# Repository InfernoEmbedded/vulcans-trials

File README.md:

# 🔥 Vulcan's Trials (`vulcans-trials`)

**Vulkan GPU + Multithreaded CPU Auto-Placer & Auto-Router for KiCad**  
Published by **InfernoEmbedded** — Licensed under **GNU GPLv3 (`GPL-3.0-only`)**

---

<p align="center">
  
  <br>
  <em>▶️ <b>Watch Vulcan's Trials in Action:</b> Real-time 1080p Auto-Placement & Auto-Routing on the 4-layer P1P2ESP board (Click to play on YouTube)</em>
</p>

---

## Overview

**Vulcan's Trials** is a unified, hardware-accelerated PCB Auto-Placer and Auto-Router written in Rust for KiCad (`8.0` / `9.0` / `10.0`). It combines:

1. **Schematic-Aware Parallel Tempering Auto-Placer (`src/placer.rs`):**
   - Automatically parses sibling `.kicad_sch` files to extract functional circuit clusters (e.g., Buck Converter, Surge/ESD Front-End, Transceiver, MCU) and passive decoupling/bias affinities.
   - Enforces exact polygon courtyard clearances using Separating Axis Theorem (SAT) collision detection (`0` courtyard overlaps) while respecting locked components and off-board RF antenna overhang zones.
   - Minimizes ratsnest topological crossings and Euclidean Minimum Spanning Tree (MST) wirelength across all CPU cores using Parallel Tempering Simulated Annealing.

2. **Vulkan Compute + Negotiated-Congestion 3D Auto-Router (`src/vulkan.rs`, `src/router.rs`):**
   - Explicitly targets **Vulkan** (`wgpu::Backends::VULKAN`) with WGSL compute shaders (`DISTANCE_FIELD_WGSL`) to accelerate 2D obstacle Euclidean Distance Field transforms on the GPU.
   - Enforces bidirectional per-netclass clearance ($\max(\text{clearance}_A, \text{clearance}_B)$), project netclass track widths (Power, Differential Pairs, High-Speed Buses, Default), keepout zones, and fine-pitch SMD pad-to-via exclusions.
   - Generates deterministic staggered pin-escape stubs ($\Delta \ge 0.75\text{ mm}$) for fine-pitch QFN, BGA, and USB-C packages, plus automated ground-plane via stitching.
   - Supports dynamic component nudging (`NudgeEngine`) and multi-pass PathFinder negotiated-congestion rip-up and reroute.

3. **Real-Time Interactive GUI (`src/gui.rs`):**
   - Live 2D PCB viewport with pan/zoom, layer toggles (`F.Cu`, `B.Cu`, Courtyards, Ratsnest, Vias, Keepouts, Reference Designators), and live trial progress.
   - Real-time **CPU Load %** (`/proc/stat`) and **Vulkan GPU Load %** (`VulkanEngine` compute duty cycle + `nvidia-smi` / DRM sysfs) gauges and sparkline histories.

---

## Quick Start

### 1. Build Release Binary & Run Self-Test
```bash
git clone https://github.com/InfernoEmbedded/vulcans-trials.git
cd vulcans-trials
cargo build --release
./target/release/vulcans-trials --self-test
```

### 2. Launch the Interactive GUI
```bash
./target/release/vulcans-trials --input /path/to/board.kicad_pcb --output /path/to/board_routed.kicad_pcb
```

### 3. Run in Headless CLI Mode
```bash
# Auto-route only
./target/release/vulcans-trials --headless --mode route \
  --input /path/to/board.kicad_pcb \
  --output /path/to/board_routed.kicad_pcb

# Full Trial (Auto-Place + Auto-Route)
./target/release/vulcans-trials --headless --mode both --duration 30 \
  --input /path/to/board.kicad_pcb \
  --output /path/to/board_vulcan.kicad_pcb
```

### 4. KiCad Action Plugin Installation

#### Option A: KiCad Plugin and Content Manager (PCM)
In KiCad (8.0, 9.0, or 10.0), open **Plugin and Content Manager → Settings (gear icon) → Add Repository** and add:
```
https://infernoembedded.github.io/vulcans-trials/repository.json
```
Then search for **Vulcan's Trials** and click **Install**.

#### Option B: Manual Plugin Symlink
Symlink `kicad_plugin` into your KiCad scripting plugins directory:
```bash
ln -s "$(pwd)/kicad_plugin" ~/.local/share/kicad/10.0/scripting/plugins/vulcans_trials
```

---

## End-to-End Tutorial & Sample Project
See [`TUTORIAL.md`](./TUTORIAL.md) for a complete walkthrough of designing a schematic with numbered functional clusters (`1. USB & UART BRIDGE`, `2. 3.3V LDO POWER`, `3. ESP32-C3 MCU`, `4. 1-WIRE SENSOR`) and schematic decoupling capacitor affinity, locking fixed edge components on the PCB (`J1`, `U3` with antenna overhang + keepout, `J2`), and auto-placing and auto-routing the board with Vulcan's Trials.

The full sample KiCad 10 project and matching ESPHome firmware configuration are located in [`examples/esphome_1wire_sensor/`](./examples/esphome_1wire_sensor/).

---

## Commercial Feature Comparison & Roadmap
See [`ROADMAP.md`](./ROADMAP.md) for the full feature comparison against commercial EDA autorouters (Cadence Allegro / Specctra, Altium ActiveRoute, Siemens Xpedition, Zuken CR-8000, Eremex TopoR) and the 6-phase development roadmap.

## License
This project is licensed under the **GNU General Public License v3.0 only** (`GPL-3.0-only`). See [`LICENSE`](./LICENSE) for full terms.

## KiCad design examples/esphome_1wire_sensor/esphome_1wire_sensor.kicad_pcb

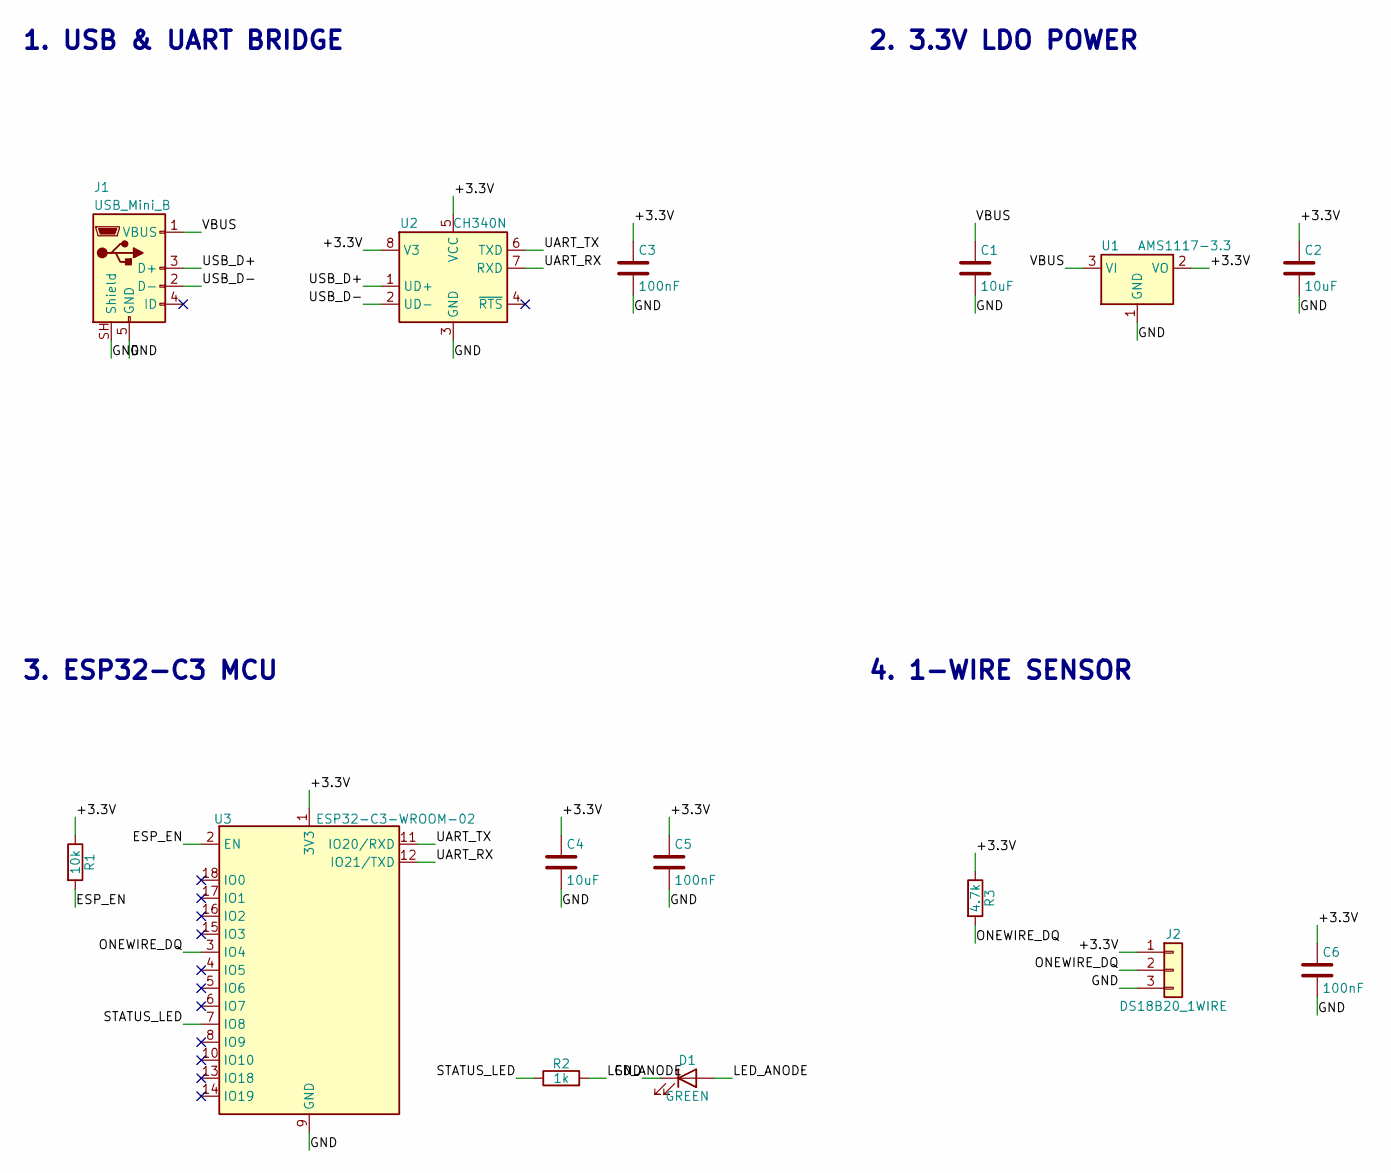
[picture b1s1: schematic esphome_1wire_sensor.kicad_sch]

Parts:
C1, C2, C4: 10uF; C_0603_1608Metric
C3, C5, C6: 100nF; C_0603_1608Metric
D1: GREEN; LED_0603_1608Metric
J1: USB_Mini_B; USB_Mini-B_Wuerth_65100516121_Horizontal
J2: DS18B20_1WIRE; PinHeader_1x03_P2.54mm_Vertical_SMD_Pin1Left
R1: 10k; R_0603_1608Metric
R2: 1k; R_0603_1608Metric
R3: 4.7k; R_0603_1608Metric
U1: AMS1117-3.3; SOT-223-3_TabPin2
U2: CH340N; JEITA_SOIC-8_3.9x4.9mm_P1.27mm
U3: ESP32-C3-WROOM-02

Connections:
/+3.3V: C2.1, C3.1, C4.1, C5.1, C6.1, J2.1, R1.1, R3.1, U1.2 (VO), U2.5 (VCC), U2.8 (V3), U3.1 (3V3)
/ESP_EN: R1.2, U3.2 (EN)
/GND: C1.2, C2.2, C3.2, C4.2, C5.2, C6.2, D1.1 (K), J1.5 (GND), J1.SH (Shield), J2.3, U1.1 (GND), U2.3 (GND), U3.9 (GND), U3.19 (GND)
/LED_ANODE: D1.2 (A), R2.2
/ONEWIRE_DQ: J2.2, R3.2, U3.3 (IO4)
/STATUS_LED: R2.1, U3.7 (IO8)
/UART_RX: U2.7 (RXD), U3.12 (IO21/TXD)
/UART_TX: U2.6 (TXD), U3.11 (IO20/RXD)
/USB_D+: J1.3 (D+), U2.1 (UD+)
/USB_D-: J1.2 (D-), U2.2 (UD-)
/VBUS: C1.1, J1.1 (VBUS), U1.3 (VI)

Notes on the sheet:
1. USB & UART BRIDGE
2. 3.3V LDO POWER
3. ESP32-C3 MCU
4. 1-WIRE SENSOR

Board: 2 copper layers, 15 parts (0 on the bottom side), 11 nets, no tracks yet.

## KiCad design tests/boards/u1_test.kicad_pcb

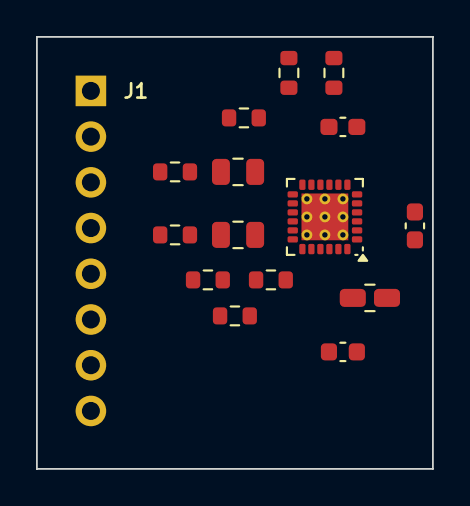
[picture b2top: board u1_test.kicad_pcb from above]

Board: 4 copper layers, 22.0 x 24.0 mm, 16 parts (0 on the bottom side), 19 nets, no tracks yet.

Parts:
C1, C2: 0.1uF 50V; C_0603_1608Metric
C3, C4: 10uF 25V; C_0805_2012Metric
C5: 1uF 16V; C_0603_1608Metric
C6: 22uF 25V; C_0805_2012Metric
J1: TEST_CONN; PinHeader_1x08_P2.54mm_Vertical
R1, R2: 4.7R; R_0603_1608Metric
R3: 1k; R_0603_1608Metric
R4: 82R; R_0603_1608Metric
R5: 62k; R_0603_1608Metric
R6: 82k; R_0603_1608Metric
R7, R8: 10k; R_0603_1608Metric
U1: MAX22088GTG+; TQFN-24-1EP_4x4mm_P0.5mm_EP2.6x2.6mm_ThermalVias

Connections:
AIO: C3.2, R3.1, U1.21
BIO: C4.2, R3.2, R4.1, U1.17
GND: C5.2, C6.2, J1.7, J1.8, R5.1, R8.2, U1.15, U1.18, U1.19, U1.22, U1.25
HN: J1.4, R2.1, U1.16
HP: J1.3, R1.1, U1.14
unnamed: C3.1, R1.2
unnamed: C4.1, R2.2
unnamed: C2.1, U1.2
unnamed: C1.1, U1.7
unnamed: C2.2, U1.3
unnamed: C1.2, U1.8
unnamed: R5.2, U1.12
P1P2_RX: J1.2, U1.5
P1P2_TX: J1.1, U1.1
TERM: R4.2, U1.23
TVL: R6.2, R7.1, U1.20
TVT: R7.2, R8.1, U1.11
VCC_5V: C5.1, J1.6, R6.1, U1.6
VRAW: C6.1, J1.5, U1.9, U1.24
